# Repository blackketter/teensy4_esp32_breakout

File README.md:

A companion sidecar board with an ESP32 module to mate with the [Teensy 4 Header Breakout Board](https://github.com/blackketter/teensy4_header_breakout).  

It's designed to solder to the bottom 8 pins on the right side of the Teensy 4 Header Breakout. 

By default it can be powered by the 3.3v power supply on the Teensy, but this may be insufficient for WiFi transmission.  In that case, populate the power supply parts (C4, C5, U2), cut the 3.3v jumper and provide 5v to the indicated pin.

There's an LED on ESP32 pin IO22.

Designed in KiCad.

Notes:

- In progress: First version worked, this version in progress.
- With longer header pins you should be able to flip the board to be under or over the Teensy 4.0
- Latest revision connects Teensy pin 28 to ESP32 EN

Pinout:

Column 1:

1. Teensy D25/RX6, ESP32 TX0/IO1
2. Teensy D26, ESP32 IO0
3. Teensy D28, ESP32 EN (Reset), On/Off
4. Teensy D24/TX6, ESP32 RX0/IO2
5. Teensy 3.3v
6. GND

Column 2:

1. GND
2. ESP32 IO18/SCK
3. ESP32 IO5/CS
4. ESP32 IO14/MOSI
5. ESP32 IO23/MISO
6. ESP32 IO32/ESP_BUSY

Column 3:

1. 3.3v Regulated Output (if using onboard regulator)
2. 5v Input To Regulator
3. ESP32 IO25, Green LED out
4. ESP32 IO26, Red LED out
5. ESP32 IO27, Blue LED out
6. ESP32 IO33

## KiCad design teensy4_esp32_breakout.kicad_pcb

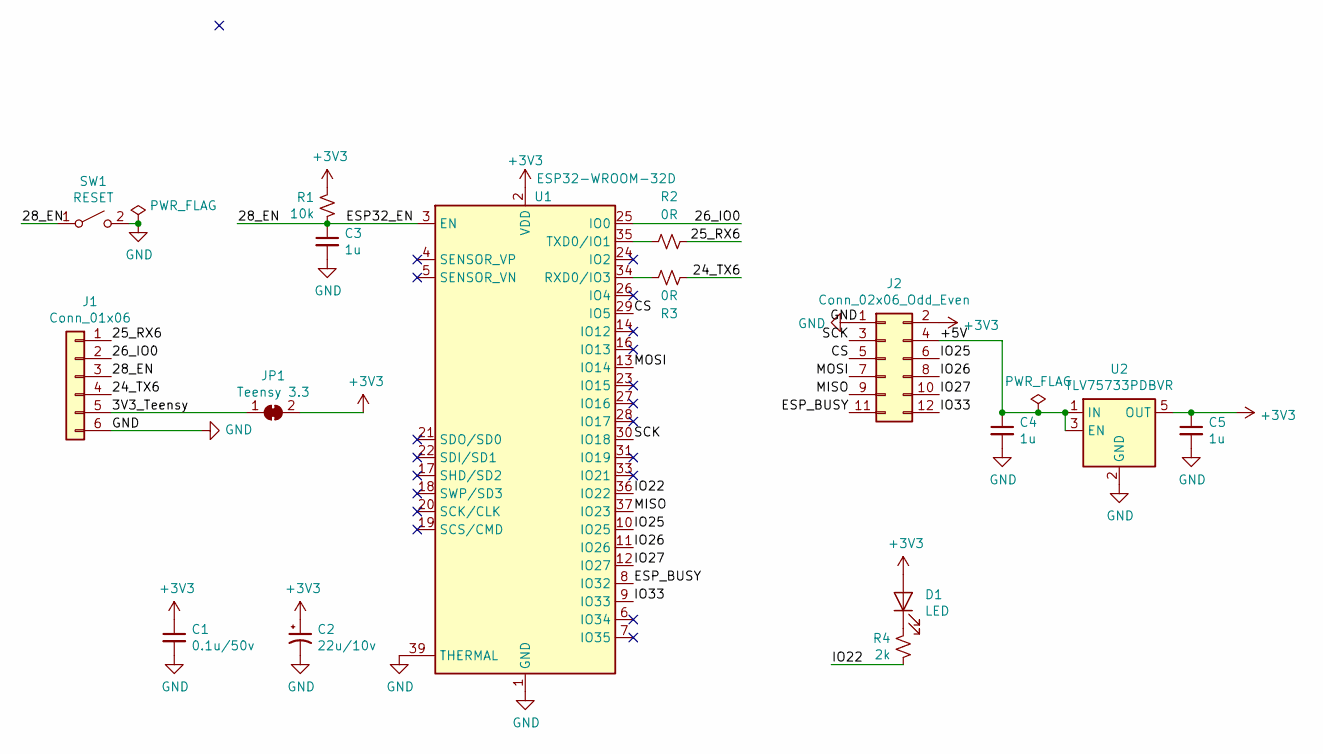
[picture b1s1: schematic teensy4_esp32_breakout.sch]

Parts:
C1: 0.1u/50v; C_0805_2012Metric_Pad1.15x1.40mm_HandSolder
C2: 22u/10v; CP_EIA-2012-12_Kemet-R_Pad1.30x1.05mm_HandSolder
C3, C4, C5: 1u; C_0805_2012Metric_Pad1.15x1.40mm_HandSolder
D1: LED; LED_0805_2012Metric_Pad1.15x1.40mm_HandSolder
J1: Conn_01x06; PinHeader_1x06_P2.54mm_Vertical
J2: Conn_02x06_Odd_Even; PinHeader_2x06_P2.54mm_Vertical
JP1: Teensy 3.3; SolderJumper-2_P1.3mm_Bridged_RoundedPad1.0x1.5mm
R1: 10k; R_0805_2012Metric_Pad1.15x1.40mm_HandSolder
R2, R3: 0R; R_0805_2012Metric_Pad1.15x1.40mm_HandSolder
R4: 2k; R_0805_2012Metric_Pad1.15x1.40mm_HandSolder
SW1: RESET; Panasonic_EVQPUJ_EVQPUA
U1: ESP32-WROOM-32D; ESP32-WROOM-32
U2: TLV75733PDBVR; SOT-23-5

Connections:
+3V3: C1.1, C2.1, C5.1, D1.2 (A), J2.2, JP1.2 (B), R1.2, U1.2 (VDD), U2.5 (OUT)
/3V3_Teensy: J1.5, JP1.1 (A)
/24_TX6: J1.4, R3.1
/25_RX6: J1.1, R2.1
/26_IO0: J1.2, U1.25 (IO0)
/28_EN: C3.1, J1.3, R1.1, SW1.1 (A), U1.3 (EN)
/+5V: C4.1, J2.4, U2.1 (IN), U2.3 (EN)
/CS: J2.5, U1.29 (IO5)
/ESP_BUSY: J2.11, U1.8 (IO32)
/IO22: R4.1, U1.36 (IO22)
/IO25: J2.6, U1.10 (IO25)
/IO26: J2.8, U1.11 (IO26)
/IO27: J2.10, U1.12 (IO27)
/IO33: J2.12, U1.9 (IO33)
/MISO: J2.9, U1.37 (IO23)
/MOSI: J2.7, U1.13 (IO14)
/SCK: J2.3, U1.30 (IO18)
GND: C1.2, C2.2, C3.2, C4.2, C5.2, J1.6, J2.1, SW1.2 (B), U1.1 (GND), U1.15 (GND), U1.38 (GND), U1.39 (THERMAL), U2.2 (GND)
unnamed: D1.1 (K), R4.2
unnamed: R2.2, U1.35 (TXD0/IO1)
unnamed: R3.2, U1.34 (RXD0/IO3)

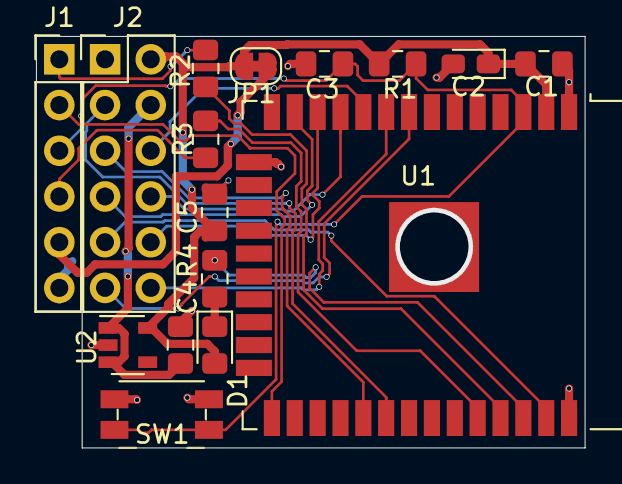
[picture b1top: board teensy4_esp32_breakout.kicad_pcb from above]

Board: 2 copper layers, 30.5 x 22.9 mm, 16 parts (0 on the bottom side), 21 nets.

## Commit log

2019-09-24 First draft
2019-09-24 Add draft bom
2019-09-24 Add PDF schematic
2019-09-24 Forgot to save
2019-09-25 Ordered this board with fix to remove double via and ground the BFV under ESP32
2019-09-25 fix regulator part number
2019-09-25 Added two more pins from ESP32 to header, including pin used for ESP_BUSY by WiFiNINA
2019-09-25 Fix missing wire, update silkscreen & readme
2019-10-11 Updates to remove program/on_off pin connections
2019-10-20 Added schematic
2021-01-10 Update README.md
    Fixed typo on ESP32 IO5/CS pin. Thanks @EsserPrototyping!
